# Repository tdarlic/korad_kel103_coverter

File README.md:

# KORAD KEL103 DC Electronic Load Banana Jack/Plug Converter

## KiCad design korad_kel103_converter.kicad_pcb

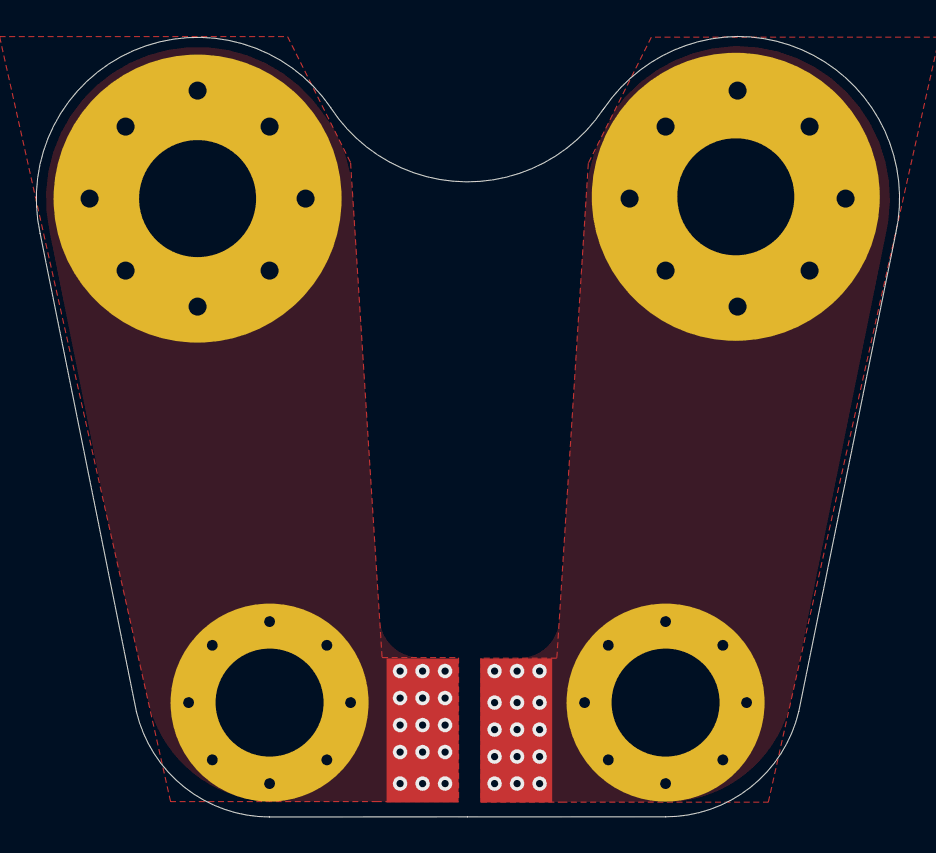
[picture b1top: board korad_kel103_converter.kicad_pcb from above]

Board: 2 copper layers, 47.9 x 43.4 mm, 6 parts (0 on the bottom side), 2 nets, no tracks yet.

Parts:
J1, J2: Conn_01x01_Female; electronic_load_conn
J3, J4: Conn_01x01_Female; MountingHole_6mm_Pad_Via
J5, J6: Conn_01x01_Female; SMD_pad_connector

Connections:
unnamed: J1.1, J3.1, J6.1
unnamed: J2.1, J4.1, J5.1

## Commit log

2021-09-09 Adding readme
2021-09-09 Creating gerbers and ordering PCB
